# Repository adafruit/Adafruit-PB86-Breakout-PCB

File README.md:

## Adafruit PB86 Step Switch Breakout-Friendly Breakout PCB

<a href="http://www.adafruit.com/products/5631"><br/>
Click here to purchase one from the Adafruit shop</a>

PCB files for the Adafruit PB86 Step Switch Breakout-Friendly Breakout PCB. 

Format is EagleCAD schematic and board layout
* https://www.adafruit.com/product/5631

### Description

A couple of months ago we started carrying packs of colorful step switches reminiscent of the 16-step sequencer keys on TR-808 synthesizers. We gave folks the heads up that the switches are not breadboard or perf-board friendly i.e. would need to either be hand-wired or designed into a PCB.

And then we heard LCD Soundsystem is coming back on tour - so we sold our guitars to buy turntables & got cracking on a break-apart panel of step-switches to evoke the spirit of electronic music and DIY venues.

Each panel comes with 12 individual breakouts to solder up and assemble to your favorite breadboard, perf-board, etc. It's a ton easier than trying to get a drink order in at the club in Bushwick, you get an easy way to get started on a DIY synth project!

Please note, each order comes with one sheet of assembled PCBs that can be broken apart - we include top and bottom railing bits to help keep it nice and flat during shipment.

Does not include headers which you'll need if you're going to plug these into a breadboard

### License

Adafruit invests time and resources providing this open source design, please support Adafruit and open-source hardware by purchasing products from [Adafruit](https://www.adafruit.com)!

Designed by Limor Fried/Ladyada for Adafruit Industries.

Creative Commons Attribution/Share-Alike, all text above must be included in any redistribution. 
See license.txt for additional details.

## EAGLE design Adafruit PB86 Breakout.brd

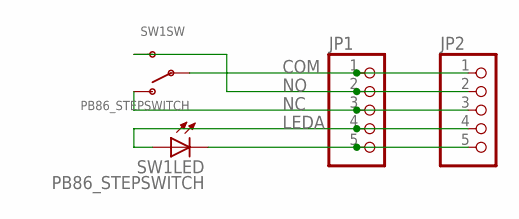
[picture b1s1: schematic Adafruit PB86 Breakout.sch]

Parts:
JP1, JP2: HEADER-1X5ROUND; 1X05_ROUND
SW1: PB86_STEPSWITCH; PB86

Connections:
COM: JP1.1, JP2.1, SW1.1A, SW1.1B
LEDA: JP1.4, JP2.4, SW1.LED+ (A)
LEDC: JP1.5, JP2.5, SW1.LED- (C)
NC: JP1.3, JP2.3, SW1.3 (O)
NO: JP1.2, JP2.2, SW1.2 (S)

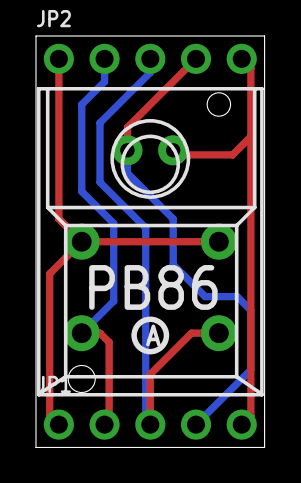
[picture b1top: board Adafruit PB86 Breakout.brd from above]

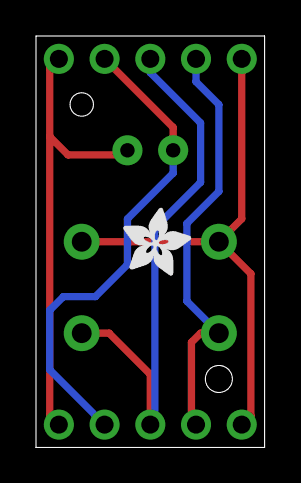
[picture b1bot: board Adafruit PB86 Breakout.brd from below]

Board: 2 copper layers, 12.7 x 22.9 mm, 25 parts (11 on the bottom side), 5 nets.

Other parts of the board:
PLABEL0: PLABEL0
PLABEL1: PLABEL1
PLABEL2: PLABEL2
PLABEL3: PLABEL3
PLABEL4: PLABEL4
PLABEL5: PLABEL5
PLABEL6: PLABEL6
PLABEL7: PLABEL7
PLABEL8: PLABEL8
PLABEL9: PLABEL9
PLABEL10: PLABEL10
PLABEL11: PLABEL11
PLABEL12: PLABEL12
PLABEL13: PLABEL13
PLABEL14: PLABEL14
PLABEL15: PLABEL15
PLABEL16: PLABEL16
PLABEL17: PLABEL17
PLABEL18: PLABEL18
PLABEL19: PLABEL19
U$1: PCBFEAT-REV-040
U$32: ADAFRUIT_3.5MM

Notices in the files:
parts and their libraries:
microbuilder: This work is placed in the public domain, and may be freely used for commercial and non-commercial work with the following conditions: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
